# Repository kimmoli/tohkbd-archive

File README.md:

OBSOLETE
========

This repository is archive only

Please see https://github.com/kimmoli/tohkbd for latest version of daemon.

PCB Files are latest.

STL Files, check dirkvl for possible changes - these are not updated.

tohkbd
======

Jolla TOH keyboard

NEW! RPM installer. <br>
Download tohkbd-<version>.rpm to the phone and install `pkcon install-local tohkbd-<version>.rpm`<br>
Installer will automatically start (and enable autostarting) the tohkbd daemon.

Folder | Waht there?
-------|-------------------------------------
bin    | Executable and rpm<br> Copy file __tohkbd__ to __/home/nemo/test__ folder and give it execute rights (`chmod 755 tohkbd`)<br> Folder can be changed by editing __tohkbd.service__ file
config | System configuration files (systemd) <br> You need root rights to copy these files in place (`devel-su`). <br> __tohkbd.service__ goes to __/etc/systemd/system/__
vkb    | Virtual keyboard to assist external keyboard with clipboard etc. <br> these files goes to __/usr/share/maliit/plugins/com/jolla/layouts/__<br> Note that you might need to restart maliit (not root) `systemctl --user restart maliit-server.service` and possible to check TOHKBD in Settings->Input...
pcb    | Eagle files (Schematic, Board)
stl    | 3D Models for printing
daemon | Sources for daemon. QtCreator project, just build (no deployment)

To get the service started (root) `systemctl start tohkbd.service`

To check is the service running (root) `systemctl status tohkbd.service` and it should say  Active: active (running)

To follow daemon log output `journalctl _SYSTEMD_UNIT=tohkbd.service -f`

*NOTE* <br>If you update binary only, you need to `systemctl stop tohkbd.service` before replacing binary file. <BR>After that you need to start it again with `systemctl start tohkbd.service`

Note that all key presses are logged so take that into account when entering passwords, etc if you also plan to post your device's logfiles to the internet.

More stuff here https://www.dropbox.com/sh/fxocsudk5gd8chs/q587RKRDhk/QWERTY%20OH

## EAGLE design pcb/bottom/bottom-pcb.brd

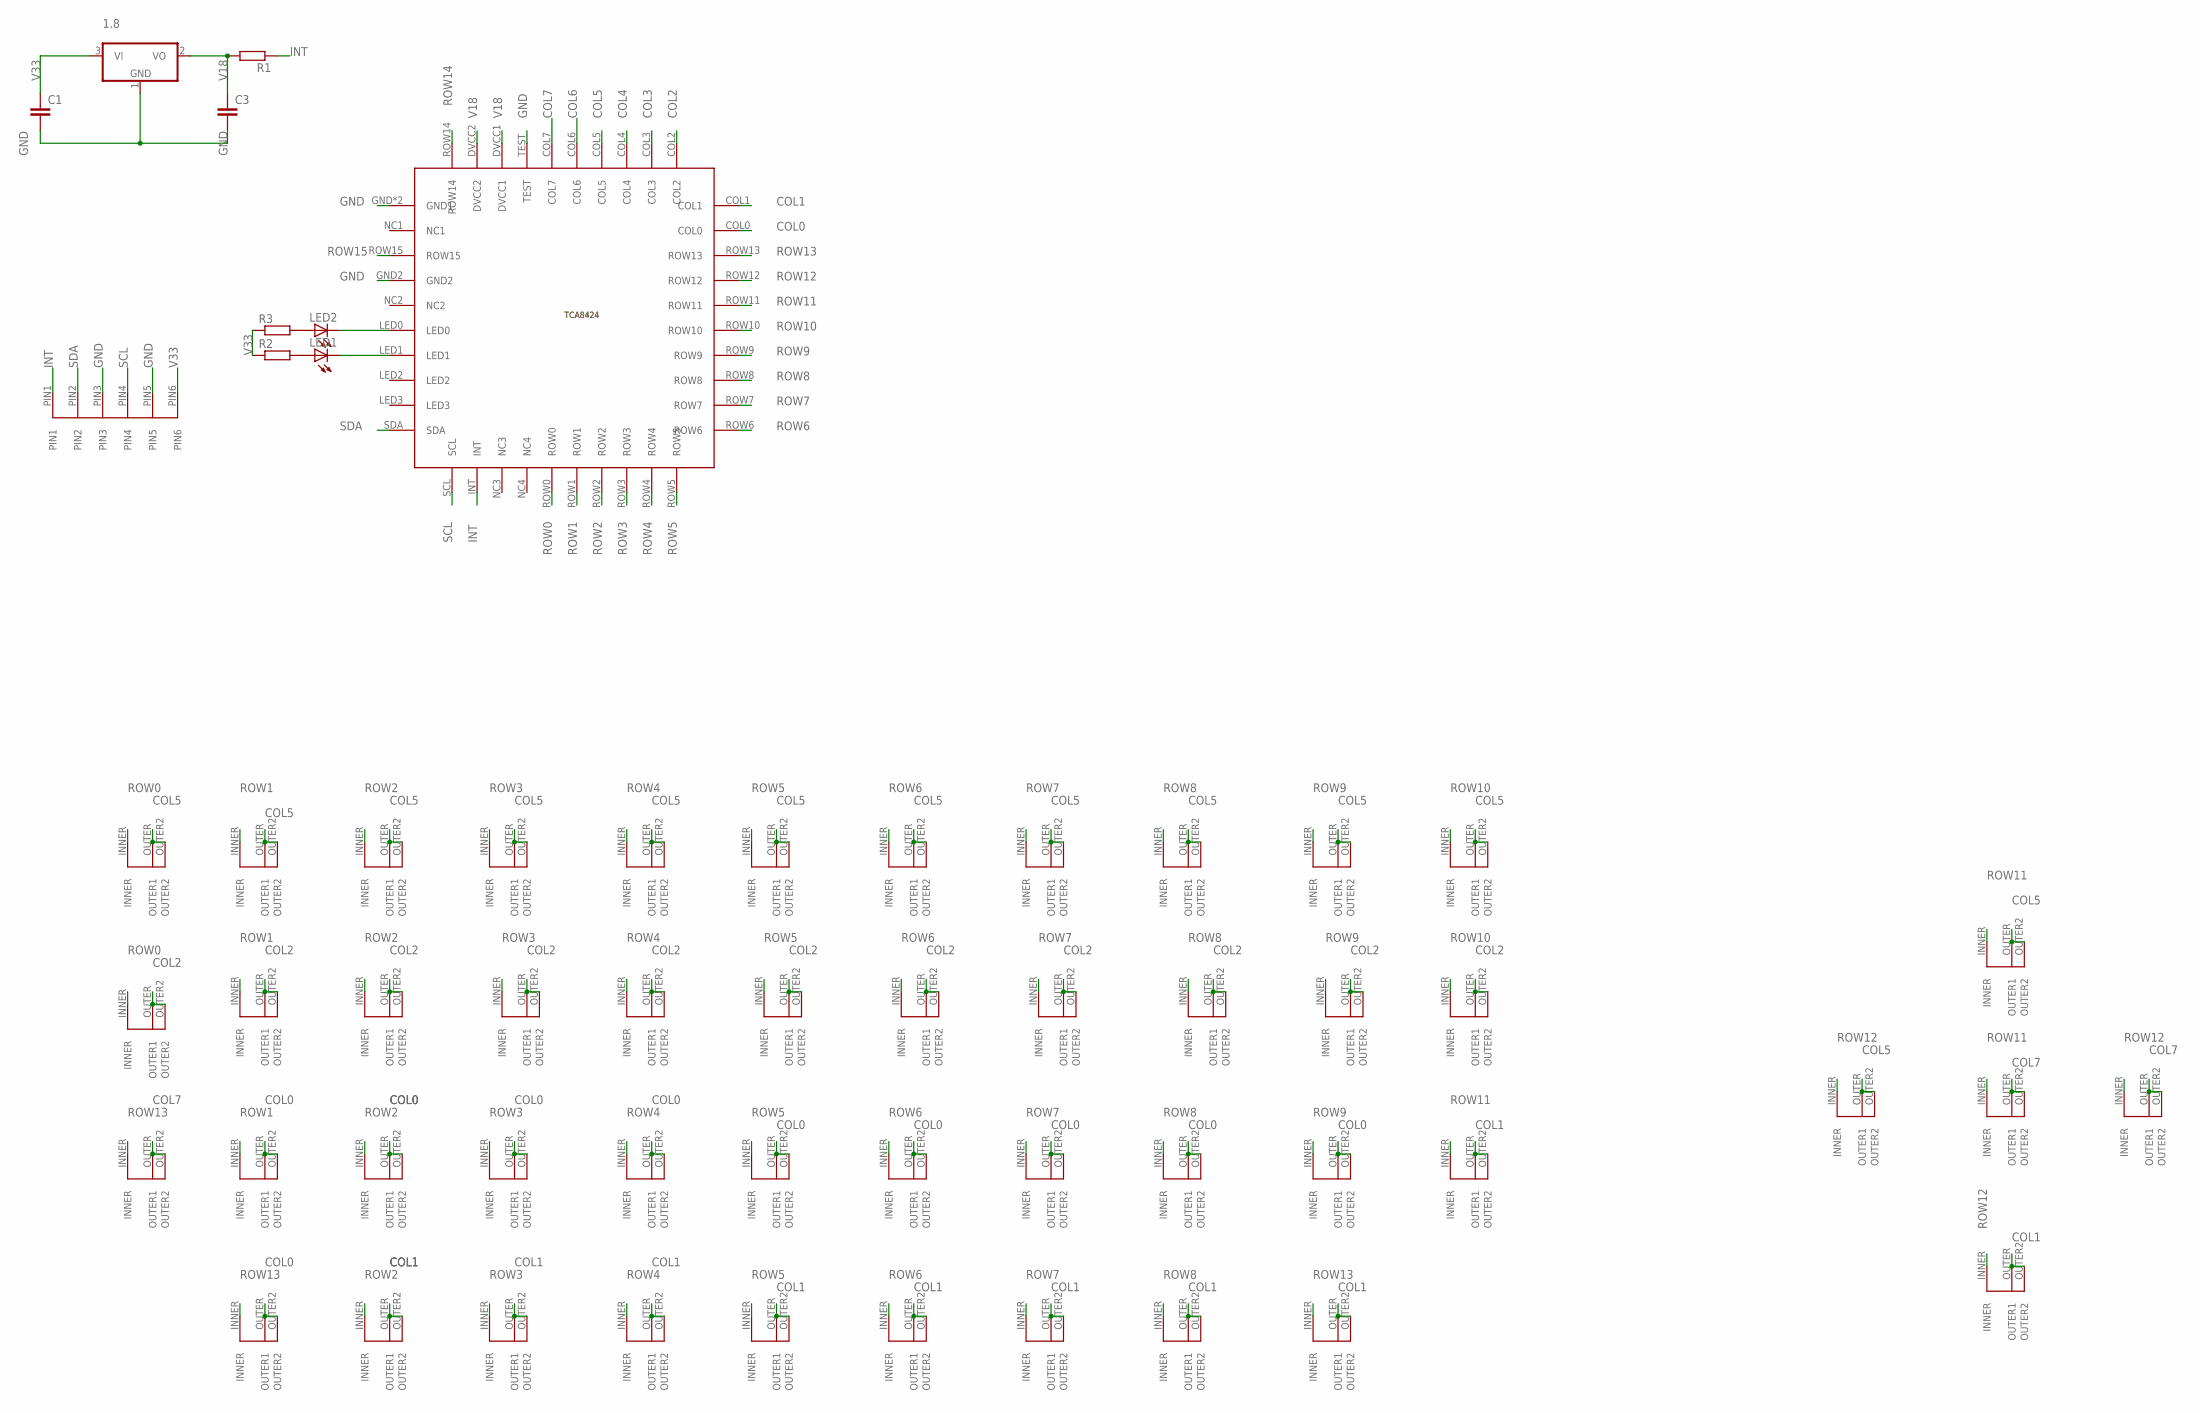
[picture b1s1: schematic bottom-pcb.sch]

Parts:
1.8: SOT23
?: BUTTON
A: BUTTON
ARROWDOWN: BUTTON
ARROWLEFT: BUTTON
ARROWRIGHT: BUTTON
ARROWUP: BUTTON
AT: BUTTON
B: BUTTON
C: BUTTON
C1, C3: C-EUC0603; C0603
D: BUTTON
DEL: BUTTON
E3: BUTTON
ENTER: BUTTON
F: BUTTON
G: BUTTON
H: BUTTON
I8: BUTTON
J: BUTTON
K: BUTTON
KOMMA: BUTTON
L: BUTTON
LED1, LED2: LEDCHIPLED_0603; CHIPLED_0603
LEFT-ALT: BUTTON
LIST: BUTTON
M: BUTTON
N: BUTTON
O9: BUTTON
OK: BUTTON
P0: BUTTON
PUNT: BUTTON
Q1: BUTTON
R1, R2, R3: R-EU_R0603; R0603
R4: BUTTON
RIGHT-ALT: BUTTON
S: BUTTON
SEARCH: BUTTON
SHIFT, SHIFT2: BUTTON
SLASH: BUTTON
SPACE1, SPACE2, SPACE3: BUTTON
T5: BUTTON
TCA8424-1: QFN40-TCA8424
U7: BUTTON
U$1: 6PCONNECTOR
V: BUTTON
W2: BUTTON
X: BUTTON
Y6: BUTTON
Z: BUTTON

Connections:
COL0: B.OUTER (OUTER1), B.OUTER2, C.OUTER (OUTER1), C.OUTER2, KOMMA.OUTER (OUTER1), KOMMA.OUTER2, LEFT-ALT.OUTER (OUTER1), LEFT-ALT.OUTER2, M.OUTER (OUTER1), M.OUTER2, N.OUTER (OUTER1), N.OUTER2, PUNT.OUTER (OUTER1), PUNT.OUTER2, TCA8424-1.COL0, V.OUTER (OUTER1), V.OUTER2, X.OUTER (OUTER1), X.OUTER2, Z.OUTER (OUTER1), Z.OUTER2
COL1: ARROWDOWN.OUTER (OUTER1), ARROWDOWN.OUTER2, AT.OUTER (OUTER1), AT.OUTER2, LIST.OUTER (OUTER1), LIST.OUTER2, RIGHT-ALT.OUTER (OUTER1), RIGHT-ALT.OUTER2, SEARCH.OUTER (OUTER1), SEARCH.OUTER2, SHIFT2.OUTER (OUTER1), SHIFT2.OUTER2, SLASH.OUTER (OUTER1), SLASH.OUTER2, SPACE1.OUTER (OUTER1), SPACE1.OUTER2, SPACE2.OUTER (OUTER1), SPACE2.OUTER2, SPACE3.OUTER (OUTER1), SPACE3.OUTER2, TCA8424-1.COL1
COL2: ?.OUTER (OUTER1), ?.OUTER2, A.OUTER (OUTER1), A.OUTER2, D.OUTER (OUTER1), D.OUTER2, ENTER.OUTER (OUTER1), ENTER.OUTER2, F.OUTER (OUTER1), F.OUTER2, G.OUTER (OUTER1), G.OUTER2, H.OUTER (OUTER1), H.OUTER2, J.OUTER (OUTER1), J.OUTER2, K.OUTER (OUTER1), K.OUTER2, L.OUTER (OUTER1), L.OUTER2, S.OUTER (OUTER1), S.OUTER2, TCA8424-1.COL2
COL3: TCA8424-1.COL3
COL4: TCA8424-1.COL4
COL5: ARROWLEFT.OUTER (OUTER1), ARROWLEFT.OUTER2, ARROWUP.OUTER (OUTER1), ARROWUP.OUTER2, DEL.OUTER (OUTER1), DEL.OUTER2, E3.OUTER (OUTER1), E3.OUTER2, I8.OUTER (OUTER1), I8.OUTER2, O9.OUTER (OUTER1), O9.OUTER2, P0.OUTER (OUTER1), P0.OUTER2, Q1.OUTER (OUTER1), Q1.OUTER2, R4.OUTER (OUTER1), R4.OUTER2, T5.OUTER (OUTER1), T5.OUTER2, TCA8424-1.COL5, U7.OUTER (OUTER1), U7.OUTER2, W2.OUTER (OUTER1), W2.OUTER2, Y6.OUTER (OUTER1), Y6.OUTER2
COL6: TCA8424-1.COL6
COL7: ARROWRIGHT.OUTER (OUTER1), ARROWRIGHT.OUTER2, OK.OUTER (OUTER1), OK.OUTER2, SHIFT.OUTER (OUTER1), SHIFT.OUTER2, TCA8424-1.COL7
GND: 1.8.1 (GND), C1.2, C3.2, TCA8424-1.GND (GND1), TCA8424-1.GND1, TCA8424-1.GND2, TCA8424-1.TEST, U$1.PIN3, U$1.PIN5
INT: R1.1, TCA8424-1.INT, U$1.PIN1
unnamed: LED1.C, TCA8424-1.LED1
unnamed: LED2.C, TCA8424-1.LED0
unnamed: LED1.A, R2.2
unnamed: LED2.A, R3.2
ROW0: A.INNER, Q1.INNER, TCA8424-1.ROW0
ROW1: S.INNER, TCA8424-1.ROW1, W2.INNER, Z.INNER
ROW2: D.INNER, E3.INNER, SEARCH.INNER, TCA8424-1.ROW2, X.INNER
ROW3: AT.INNER, C.INNER, F.INNER, R4.INNER, TCA8424-1.ROW3
ROW4: G.INNER, SPACE1.INNER, T5.INNER, TCA8424-1.ROW4, V.INNER
ROW5: B.INNER, H.INNER, SPACE2.INNER, TCA8424-1.ROW5, Y6.INNER
ROW6: J.INNER, N.INNER, SPACE3.INNER, TCA8424-1.ROW6, U7.INNER
ROW7: I8.INNER, K.INNER, M.INNER, SLASH.INNER, TCA8424-1.ROW7
ROW8: KOMMA.INNER, L.INNER, LIST.INNER, O9.INNER, TCA8424-1.ROW8
ROW9: ?.INNER, P0.INNER, PUNT.INNER, TCA8424-1.ROW9
ROW10: DEL.INNER, ENTER.INNER, TCA8424-1.ROW10
ROW11: ARROWUP.INNER, OK.INNER, SHIFT2.INNER, TCA8424-1.ROW11
ROW12: ARROWDOWN.INNER, ARROWLEFT.INNER, ARROWRIGHT.INNER, TCA8424-1.ROW12
ROW13: LEFT-ALT.INNER, RIGHT-ALT.INNER, SHIFT.INNER, TCA8424-1.ROW13
ROW14: TCA8424-1.ROW14
ROW15: TCA8424-1.ROW15
SCL: TCA8424-1.SCL, U$1.PIN4
SDA: TCA8424-1.SDA, U$1.PIN2
V18: 1.8.2 (VO), C3.1, R1.2, TCA8424-1.DVCC1, TCA8424-1.DVCC2
V33: 1.8.3 (VI), C1.1, R2.1, R3.1, U$1.PIN6

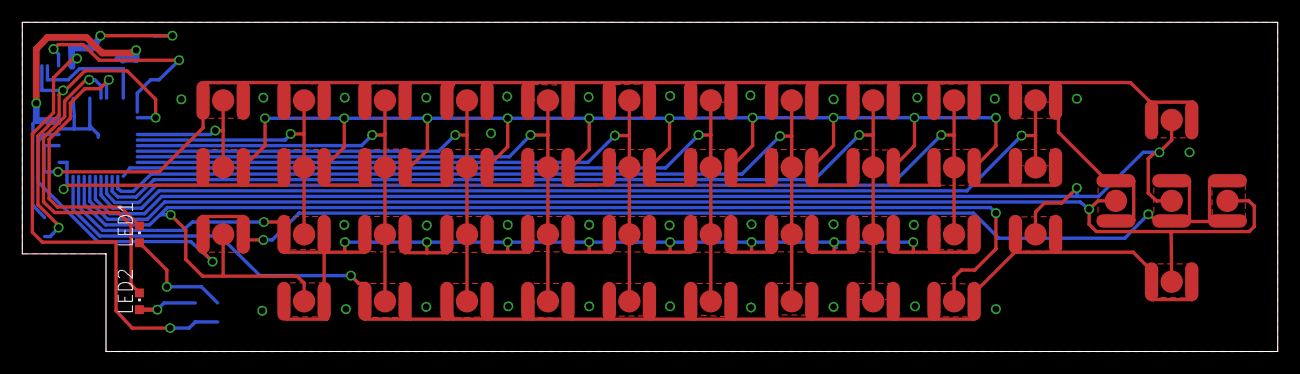
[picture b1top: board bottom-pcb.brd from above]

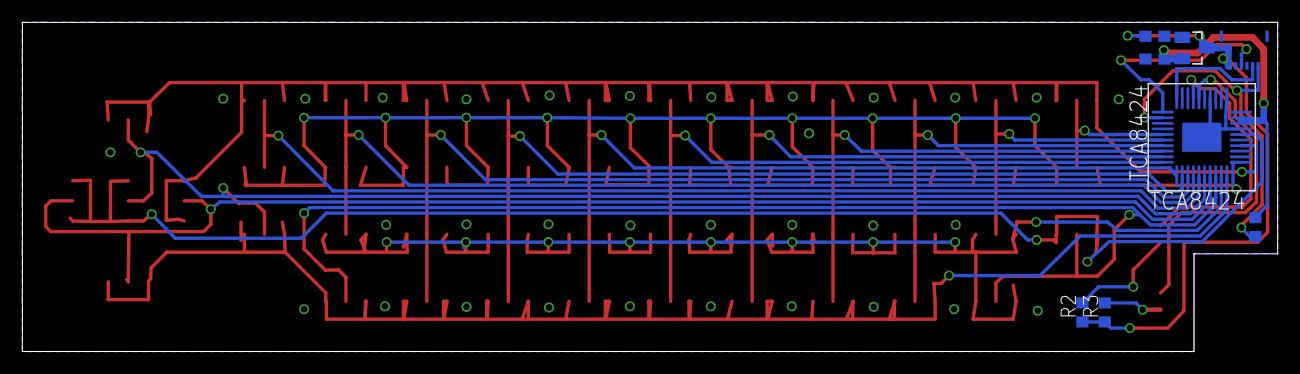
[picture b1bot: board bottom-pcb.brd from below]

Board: 4 copper layers, 112.5 x 29.5 mm, 57 parts (8 on the bottom side), 29 nets.

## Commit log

2014-03-04 Original PCB Files added
2014-03-04 first vkb version, just stripped down
2014-03-04 dbus and systemd configuration
2014-03-04 alpha.0.17 binary
2014-03-15 stl files added
2014-03-20 Import of tohkbd_daemon v0.24 sources
2014-03-20 Update README.md
    added daemon -dir
2014-03-20 daemon: use 4-space indenting everywhere
2014-03-20 daemon: replace custom writeToLog with printing to stdout
    systemd automatically forwards process stdout and stderr to the journal
    where it can be viewed. make sure to set stdout and stderr to linebuffered
    mode so the journal events are not delayed.
2014-03-20 tohkbd: map search key to control
2014-03-20 daemon: misc cleanups
    * make various things const
    * remove unused variables
2014-03-20 binary 0.25 update
2014-03-21 Create LICENSE
2014-03-21 Update LICENSE
    Added Dirk to Copyright
2014-03-21 tca8424: fix tab, question mark and caret characters
2014-03-21 tohkeyboard: disable leds by default
2014-03-21 tohkeyboard: capslock enables led
2014-03-21 tohkeyboard: free mutex if reading keyboard fails
2014-03-21 Binary 0.26 update
2014-03-22 Update tca8424.cpp
    Right control key remapped to ESC and pipe "|"
2014-03-22 Right control as backslash/pipe/ESC
    This way both missing keys are covered and ESC is still usable
2014-03-22 Fix for PageUp/PageDown
    Works in midnight commander and nano this way, not sure if proper fix
2014-03-23 Update tca8424.cpp, Right control as backslash/pipe/ESC
    This way both missing keys are covered and ESC is still usable
2014-03-23 Binary 0.27 update
2014-03-23 Sessionbus connection remove
2014-03-23 dbus config file remove. Relocate binary to /usr/sbin
2014-03-23 Binary 0.28 update
2014-03-23 RPM Installer, bin-only spec file
2014-03-25 daemon: cleanups to output error messages and silence compiler warnings
    * make sure to print an error message when opening, reading or writing to
    various files/devices fails
    * more updates for more consistent indentation and code style
    * use booleans instead of strings as arguments to internal functions
    * clean up unused includes and code
2014-03-28 Add version number define to project file
2014-03-28 Binary 0.1-29 update
2014-03-28 Added note about binary only updating
